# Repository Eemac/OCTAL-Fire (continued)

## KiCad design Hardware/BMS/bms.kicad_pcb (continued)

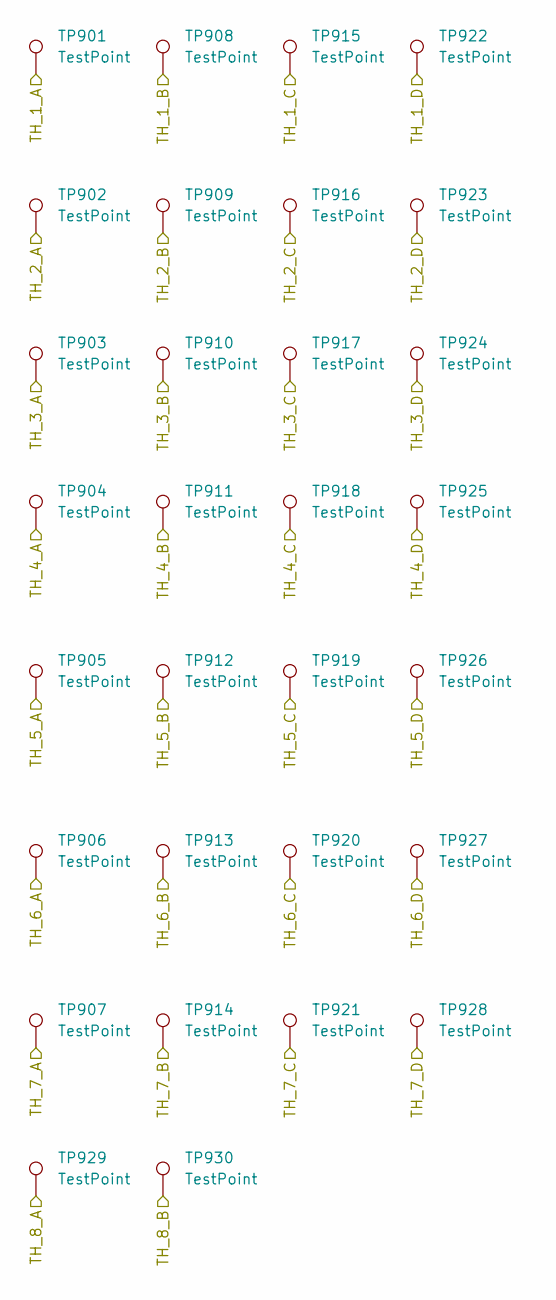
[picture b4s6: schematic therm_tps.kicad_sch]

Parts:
TP901, TP902, TP903, TP904, TP905, TP906, TP907, TP908, TP909, TP910, TP911, TP912, TP913, TP914, TP915, TP916, TP917, TP918, TP919, TP920, TP921, TP922, TP923, TP924, TP925, TP926, TP927, TP928, TP929, TP930: TestPoint; TestPoint_Pad_1.0x1.0mm

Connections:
/THERM_BUSBAR: TP929.1; also elsewhere on the board
/Thermistors/THERM_AMBIENT: TP930.1; also elsewhere on the board
/Thermistors/TH_1_A: TP901.1; also elsewhere on the board
/Thermistors/TH_1_B: TP908.1; also elsewhere on the board
/Thermistors/TH_1_C: TP915.1; also elsewhere on the board
/Thermistors/TH_1_D: TP922.1; also elsewhere on the board
/Thermistors/TH_2_A: TP902.1; also elsewhere on the board
/Thermistors/TH_2_B: TP909.1; also elsewhere on the board
/Thermistors/TH_2_C: TP916.1; also elsewhere on the board
/Thermistors/TH_2_D: TP923.1; also elsewhere on the board
/Thermistors/TH_3_A: TP917.1; also elsewhere on the board
/Thermistors/TH_3_B: TP924.1; also elsewhere on the board
/Thermistors/TH_3_C: TP903.1; also elsewhere on the board
/Thermistors/TH_3_D: TP910.1; also elsewhere on the board
/Thermistors/TH_4_A: TP904.1; also elsewhere on the board
/Thermistors/TH_4_B: TP911.1; also elsewhere on the board
/Thermistors/TH_4_C: TP918.1; also elsewhere on the board
/Thermistors/TH_4_D: TP925.1; also elsewhere on the board
/Thermistors/TH_5_A: TP905.1; also elsewhere on the board
/Thermistors/TH_5_B: TP912.1; also elsewhere on the board
/Thermistors/TH_5_C: TP919.1; also elsewhere on the board
/Thermistors/TH_5_D: TP926.1; also elsewhere on the board
/Thermistors/TH_6_A: TP906.1; also elsewhere on the board
/Thermistors/TH_6_B: TP913.1; also elsewhere on the board
/Thermistors/TH_6_C: TP920.1; also elsewhere on the board
/Thermistors/TH_6_D: TP927.1; also elsewhere on the board

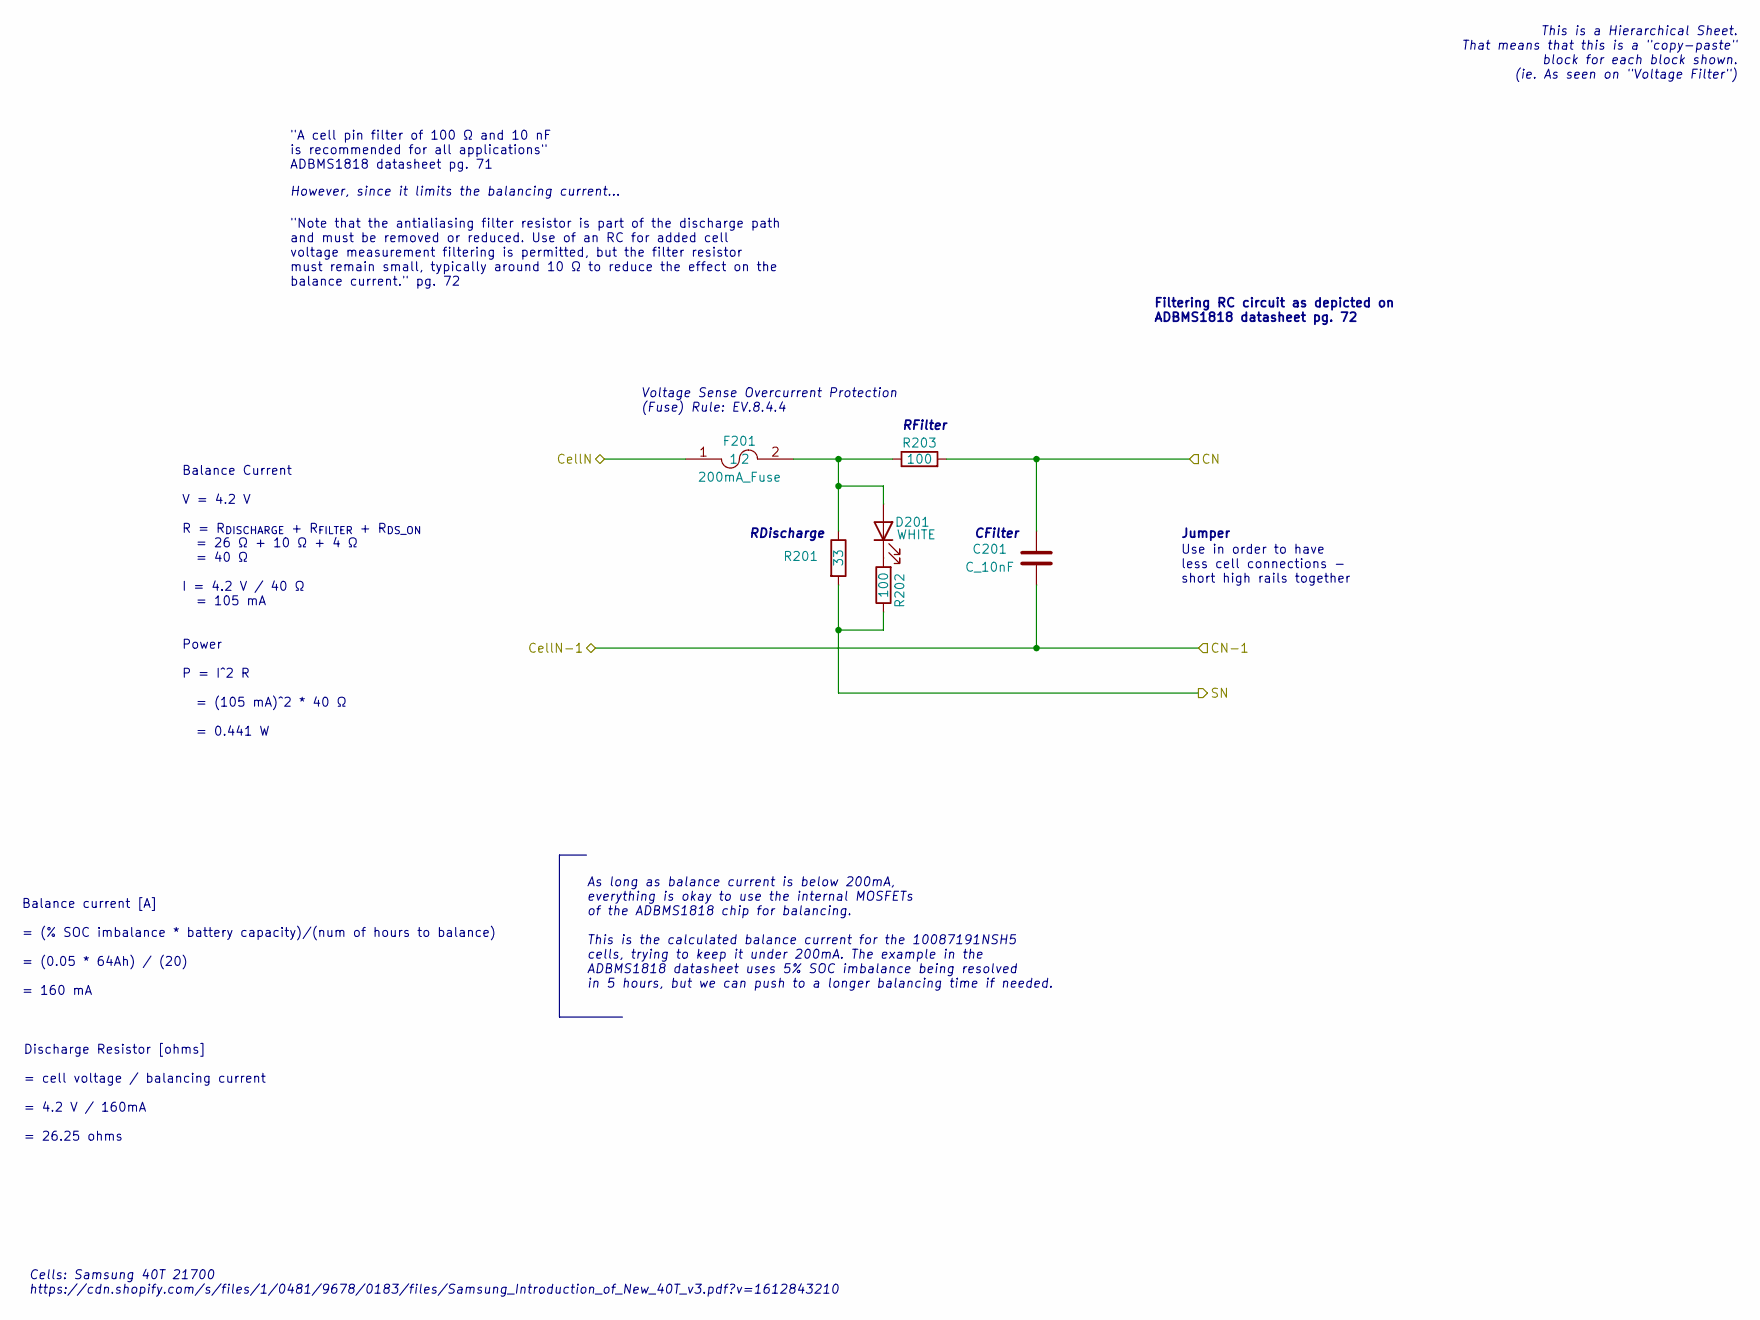
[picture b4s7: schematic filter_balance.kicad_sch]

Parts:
C201: C_10nF; C_0603_1608Metric; MPN CL10B103KB8NNNC
D201: WHITE; LED_0805_2012Metric
F201: 200mA_Fuse; Fuse_1206_3216Metric; MPN 0466.200NRHF
R201: 33; R_2512_6332Metric; MPN 352022RJT
R202: 100; R_0603_1608Metric
R203: 100; R_0603_1608Metric; MPN SG73P1JTTD100J

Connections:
/ADBMS1818/C1: C201.1, F201.1, R203.2; also elsewhere on the board
/ADBMS1818/S1: R201.2, R202.1; also elsewhere on the board
GND: C201.2; also elsewhere on the board
unnamed: D201.2 (A), F201.2, R201.1, R203.1
unnamed: D201.1 (K), R202.2

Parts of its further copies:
C701, C1001, C1201, C1301, C1401, C1501, C1601, C1701, C1801, C1901, C2001, C2101, C2201: C_10nF; C_0603_1608Metric; MPN CL10B103KB8NNNC
D701, D1001, D1201, D1301, D1401, D1501, D1601, D1701, D1801, D1901, D2001, D2101, D2201: WHITE; LED_0805_2012Metric
F701, F1001, F1201, F1301, F1401, F1501, F1601, F1701, F1801, F1901, F2001, F2101, F2201: 200mA_Fuse; Fuse_1206_3216Metric; MPN 0466.200NRHF
R701, R1001, R1201, R1301, R1401, R1501, R1601, R1701, R1801, R1901, R2001, R2101, R2201: 33; R_2512_6332Metric; MPN 352022RJT
R702, R1002, R1202, R1302, R1402, R1502, R1602, R1702, R1802, R1902, R2002, R2102, R2202: 100; R_0603_1608Metric
R703, R1003, R1203, R1303, R1403, R1503, R1603, R1703, R1803, R1903, R2003, R2103, R2203: 100; R_0603_1608Metric; MPN SG73P1JTTD100J

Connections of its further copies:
/ADBMS1818/C1: C701.2; also elsewhere on the board
/ADBMS1818/C2: C701.1, C1001.2, F701.1, R703.2; also elsewhere on the board
/ADBMS1818/C3: C1001.1, C1201.2, F1001.1, R1003.2; also elsewhere on the board
/ADBMS1818/C4: C1201.1, C1301.2, F1201.1, R1203.2; also elsewhere on the board
/ADBMS1818/C5: C1301.1, C1401.2, F1301.1, R1303.2; also elsewhere on the board
/ADBMS1818/C6: C1401.1, C1501.2, F1401.1, R1403.2; also elsewhere on the board
/ADBMS1818/C7: C1501.1, C1601.2, F1501.1, R1503.2; also elsewhere on the board
/ADBMS1818/C8: C1601.1, C1701.2, F1601.1, R1603.2; also elsewhere on the board
/ADBMS1818/C9: C1701.1, C1801.2, F1701.1, R1703.2; also elsewhere on the board
/ADBMS1818/C10: C1801.1, C1901.2, F1801.1, R1803.2; also elsewhere on the board
/ADBMS1818/C11: C1901.1, C2001.2, F1901.1, R1903.2; also elsewhere on the board
/ADBMS1818/C12: C2001.1, C2101.2, F2001.1, R2003.2; also elsewhere on the board
/ADBMS1818/C13: C2101.1, C2201.2, F2101.1, R2103.2; also elsewhere on the board
/ADBMS1818/C14: C2201.1, R2203.2; also elsewhere on the board
/ADBMS1818/CELL14: F2201.1; also elsewhere on the board
/ADBMS1818/S2: R701.2, R702.1; also elsewhere on the board
/ADBMS1818/S3: R1001.2, R1002.1; also elsewhere on the board
/ADBMS1818/S4: R1201.2, R1202.1; also elsewhere on the board
/ADBMS1818/S5: R1301.2, R1302.1; also elsewhere on the board
/ADBMS1818/S6: R1401.2, R1402.1; also elsewhere on the board
/ADBMS1818/S7: R1501.2, R1502.1; also elsewhere on the board
/ADBMS1818/S8: R1601.2, R1602.1; also elsewhere on the board
/ADBMS1818/S9: R1701.2, R1702.1; also elsewhere on the board
/ADBMS1818/S10: R1801.2, R1802.1; also elsewhere on the board
/ADBMS1818/S11: R1901.2, R1902.1; also elsewhere on the board
/ADBMS1818/S12: R2001.2, R2002.1; also elsewhere on the board
/ADBMS1818/S13: R2101.2, R2102.1; also elsewhere on the board
/ADBMS1818/S14: R2201.2, R2202.1; also elsewhere on the board
unnamed: D701.2 (A), F701.2, R701.1, R703.1
unnamed: D701.1 (K), R702.2
unnamed: D1001.2 (A), F1001.2, R1001.1, R1003.1
unnamed: D1001.1 (K), R1002.2
unnamed: D1201.2 (A), F1201.2, R1201.1, R1203.1
unnamed: D1201.1 (K), R1202.2
unnamed: D1301.2 (A), F1301.2, R1301.1, R1303.1
unnamed: D1301.1 (K), R1302.2
unnamed: D1401.2 (A), F1401.2, R1401.1, R1403.1
unnamed: D1401.1 (K), R1402.2
unnamed: D1501.2 (A), F1501.2, R1501.1, R1503.1
unnamed: D1501.1 (K), R1502.2
unnamed: D1601.2 (A), F1601.2, R1601.1, R1603.1
unnamed: D1601.1 (K), R1602.2
unnamed: D1701.2 (A), F1701.2, R1701.1, R1703.1
unnamed: D1701.1 (K), R1702.2
unnamed: D1801.2 (A), F1801.2, R1801.1, R1803.1
unnamed: D1801.1 (K), R1802.2
unnamed: D1901.2 (A), F1901.2, R1901.1, R1903.1
unnamed: D1901.1 (K), R1902.2
unnamed: D2001.2 (A), F2001.2, R2001.1, R2003.1
unnamed: D2001.1 (K), R2002.2
unnamed: D2101.2 (A), F2101.2, R2101.1, R2103.1
unnamed: D2101.1 (K), R2102.2
unnamed: D2201.2 (A), F2201.2, R2201.1, R2203.1
unnamed: D2201.1 (K), R2202.2

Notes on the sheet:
Filtering RC circuit as depicted on ADBMS1818 datasheet pg. 72
"A cell pin filter of 100 Ω and 10 nF is recommended for all applications" ADBMS1818 datasheet pg. 71
Cells: Samsung 40T 21700 https://cdn.shopify.com/s/files/1/0481/9678/0183/files/Samsung_Introduction_of_New_40T_v3.pdf?v=1612843210
Balance current [A] = (% SOC imbalance * battery capacity)/(num of hours to balance) = (0.05 * 64Ah) / (20) = 160 mA
RFilter
Discharge Resistor [ohms] = cell voltage / balancing current = 4.2 V / 160mA = 26.25 ohms
Use in order to have less cell connections - short high rails together
"Note that the antialiasing filter resistor is part of the discharge path and must be removed or reduced. Use of an RC for added cell voltage measurement filtering is permitted, but the filter resistor must remain small, typically around 10 Ω to reduce the effect on the balance current." pg. 72
However, since it limits the balancing current...
RDischarge
Balance Current V = 4.2 V R = R_{DISCHARGE} + R_{FILTER} + R_{DS_ON} = 26 Ω + 10 Ω + 4 Ω = 40 Ω I = 4.2 V / 40 Ω = 105 mA Power P = I^2 R = (105 mA)^2 * 40 Ω = 0.441 W
As long as balance current is below 200mA, everything is okay to use the internal MOSFETs of the ADBMS1818 chip for balancing. This is the calculated balance current for the 10087191NSH5 cells, trying to keep it under 200mA. The example in the ADBMS1818 datasheet uses 5% SOC imbalance being resolve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
This is a Hierarchical Sheet. That means that this is a "copy-paste" block for each block shown. (ie. As seen on "Voltage Filter")
CFilter
Voltage Sense Overcurrent Protection (Fuse) Rule: EV.8.4.4
Jumper

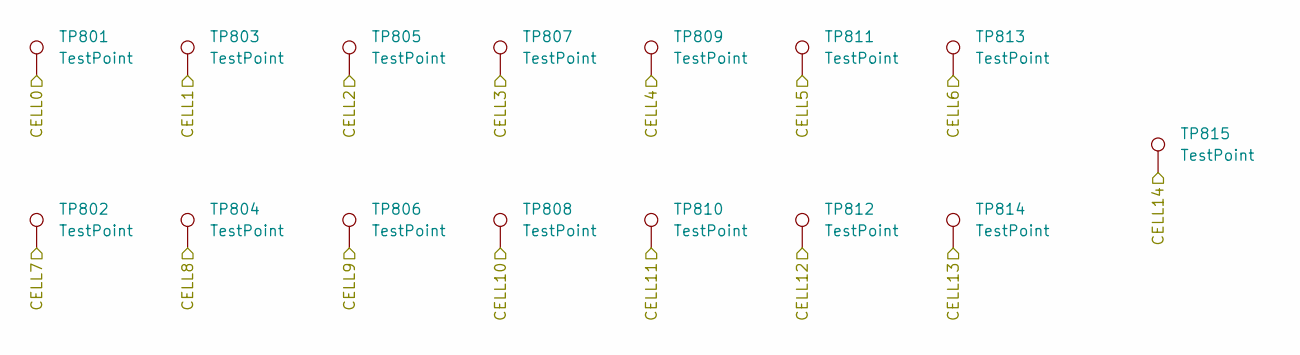
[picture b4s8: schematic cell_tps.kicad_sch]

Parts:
TP801, TP802, TP803, TP804, TP805, TP806, TP807, TP808, TP809, TP810, TP811, TP812, TP813, TP814, TP815: TestPoint; TestPoint_Keystone_5019_Miniature

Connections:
/ADBMS1818/C1: TP803.1; also elsewhere on the board
/ADBMS1818/C2: TP805.1; also elsewhere on the board
/ADBMS1818/C3: TP807.1; also elsewhere on the board
/ADBMS1818/C4: TP809.1; also elsewhere on the board
/ADBMS1818/C5: TP811.1; also elsewhere on the board
/ADBMS1818/C6: TP813.1; also elsewhere on the board
/ADBMS1818/C7: TP802.1; also elsewhere on the board
/ADBMS1818/C8: TP804.1; also elsewhere on the board
/ADBMS1818/C9: TP806.1; also elsewhere on the board
/ADBMS1818/C10: TP808.1; also elsewhere on the board
/ADBMS1818/C11: TP810.1; also elsewhere on the board
/ADBMS1818/C12: TP812.1; also elsewhere on the board
/ADBMS1818/C13: TP814.1; also elsewhere on the board
/ADBMS1818/CELL14: TP815.1; also elsewhere on the board
GND: TP801.1; also elsewhere on the board

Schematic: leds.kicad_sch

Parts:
D1101, D1104, D1106, D1109, D1111: LED_0805_Red; LED_0805_OEM; MPN 475-1415-1-ND
D1102, D1105, D1108, D1110, D1112: LED_0805; LED_0805_OEM; MPN 475-1410-1-ND
D1103: LED_0805_Amber; LED_0805_OEM; MPN L71517CT-ND
D1107: WHITE; LED_0805_2012Metric
R1101, R1104, R1106, R1109, R1111: 300; R_0603_1608Metric; MPN 667-ERJ-6ENF1200V
R1102, R1105, R1108, R1110, R1112: 120; R_0603_1608Metric; MPN 667-ERJ-6ENF1200V
R1103, R1107: 220; R_0603_1608Metric; MPN 667-ERJ-6ENF1200V

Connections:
/STM32/ADBMS_COMS: D1110.2 (A); also elsewhere on the board
/STM32/BMS_HEARTBEAT: D1107.2 (A); also elsewhere on the board
/STM32/CAN_COMS: D1102.2 (A); also elsewhere on the board
/STM32/DEBUG1: D1103.2 (A); also elsewhere on the board
/STM32/ERROR: D1111.2 (A); also elsewhere on the board
/STM32/MUX1_COMS: D1105.2 (A); also elsewhere on the board
/STM32/MUX2_COMS: D1108.2 (A); also elsewhere on the board
/STM32/OT: D1106.2 (A); also elsewhere on the board
/STM32/OV: D1101.2 (A); also elsewhere on the board
/STM32/USB_C_COMS: D1112.2 (A); also elsewhere on the board
/STM32/UT: D1109.2 (A); also elsewhere on the board
/STM32/UV: D1104.2 (A); also elsewhere on the board
GND: R1101.2, R1102.2, R1103.2, R1104.2, R1105.2, R1106.2, R1107.2, R1108.2, R1109.2, R1110.2, R1111.2, R1112.2; also elsewhere on the board
unnamed: D1101.1 (K), R1101.1
unnamed: D1102.1 (K), R1102.1
unnamed: D1103.1 (K), R1103.1
unnamed: D1104.1 (K), R1104.1
unnamed: D1105.1 (K), R1105.1
unnamed: D1106.1 (K), R1106.1
unnamed: D1107.1 (K), R1107.1
unnamed: D1108.1 (K), R1108.1
unnamed: D1109.1 (K), R1109.1
unnamed: D1110.1 (K), R1110.1
unnamed: D1111.1 (K), R1111.1
unnamed: D1112.1 (K), R1112.1

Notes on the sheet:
Heartbeat in code

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
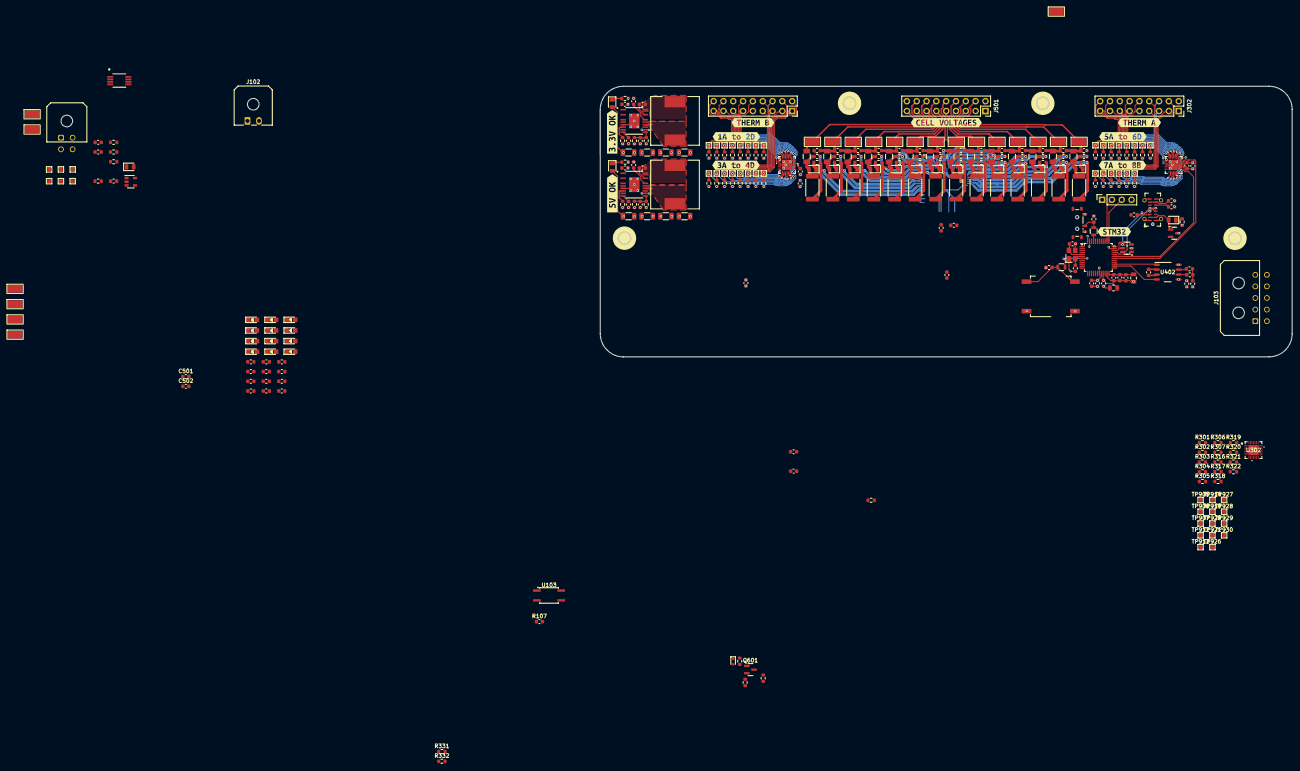
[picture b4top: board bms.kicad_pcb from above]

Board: 6 copper layers, 179.0 x 70.0 mm, 340 parts (1 on the bottom side), 181 nets.

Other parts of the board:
R301#2, R302#2, R303#2, R304#2, R305#2, R306#2, R307#2, R316#2, R317#2, R318#2, R319#2, R320#2, R321#2, R322#2: 100k; R_0603_1608Metric
TP905#2, TP906#2, TP907#2, TP912#2, TP913#2, TP914#2, TP919#2, TP920#2, TP921#2, TP926#2, TP927#2, TP928#2, TP929#2, TP930#2: TestPoint; TestPoint_Pad_1.0x1.0mm
U302#2: MAX14661ETI+T; 21-0139I_T2844-1_MXM
kibuzzard-68FE96E6: G***; kibuzzard-68FE96E6
kibuzzard-68FE9694: G***; kibuzzard-68FE9694
kibuzzard-68FE9708: G***; kibuzzard-68FE9708
kibuzzard-690BEEAD: G***; kibuzzard-690BEEAD
kibuzzard-690BEF4B: G***; kibuzzard-690BEF4B
kibuzzard-690CD8B4: G***; kibuzzard-690CD8B4
kibuzzard-690CF62F: G***; kibuzzard-690CF62F
kibuzzard-690CF63A: G***; kibuzzard-690CF63A
kibuzzard-690CF627: G***; kibuzzard-690CF627
kibuzzard-690D526F: G***; kibuzzard-690D526F

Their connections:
+3.3V: R301#2.2, R302#2.2, R303#2.2, R304#2.2, R305#2.2, R306#2.2, R307#2.2, R316#2.2, R317#2.2, R318#2.2, R319#2.2, R320#2.2, R321#2.2, R322#2.2, U302#2.22 (*SD), U302#2.26 (VCC), U302#2.28 (DOUT/A1); also elsewhere on the board
/MUX_SCL: U302#2.24 (SCLK/SCL); also elsewhere on the board
/MUX_SDA: U302#2.27 (DIN/SDA); also elsewhere on the board
/THERM_A2: U302#2.10 (COMA); also elsewhere on the board
/THERM_B2: U302#2.13 (COMB); also elsewhere on the board
/THERM_BUSBAR: R307#2.1, U302#2.17 (AB13); also elsewhere on the board
/Thermistors/THERM_AMBIENT: R322#2.1, U302#2.16 (AB14); also elsewhere on the board
/Thermistors/TH_5_A: R301#2.1, TP905#2.1, U302#2.2 (AB01); also elsewhere on the board
/Thermistors/TH_5_B: R316#2.1, TP912#2.1, U302#2.3 (AB02); also elsewhere on the board
/Thermistors/TH_5_C: R302#2.1, TP919#2.1, U302#2.4 (AB03); also elsewhere on the board
/Thermistors/TH_5_D: R317#2.1, TP926#2.1, U302#2.5 (AB04); also elsewhere on the board
/Thermistors/TH_6_A: R303#2.1, TP906#2.1, U302#2.6 (AB05); also elsewhere on the board
/Thermistors/TH_6_B: R318#2.1, TP913#2.1, U302#2.7 (AB06); also elsewhere on the board
/Thermistors/TH_6_C: R304#2.1, TP920#2.1, U302#2.8 (AB07); also elsewhere on the board
/Thermistors/TH_6_D: R319#2.1, TP927#2.1, U302#2.9 (AB08); also elsewhere on the board
GND: U302#2.1 (*SPI/I2C), U302#2.11 (GND), U302#2.23 (*CS/A0), U302#2.25 (GND), U302#2.29 (EPAD); also elsewhere on the board

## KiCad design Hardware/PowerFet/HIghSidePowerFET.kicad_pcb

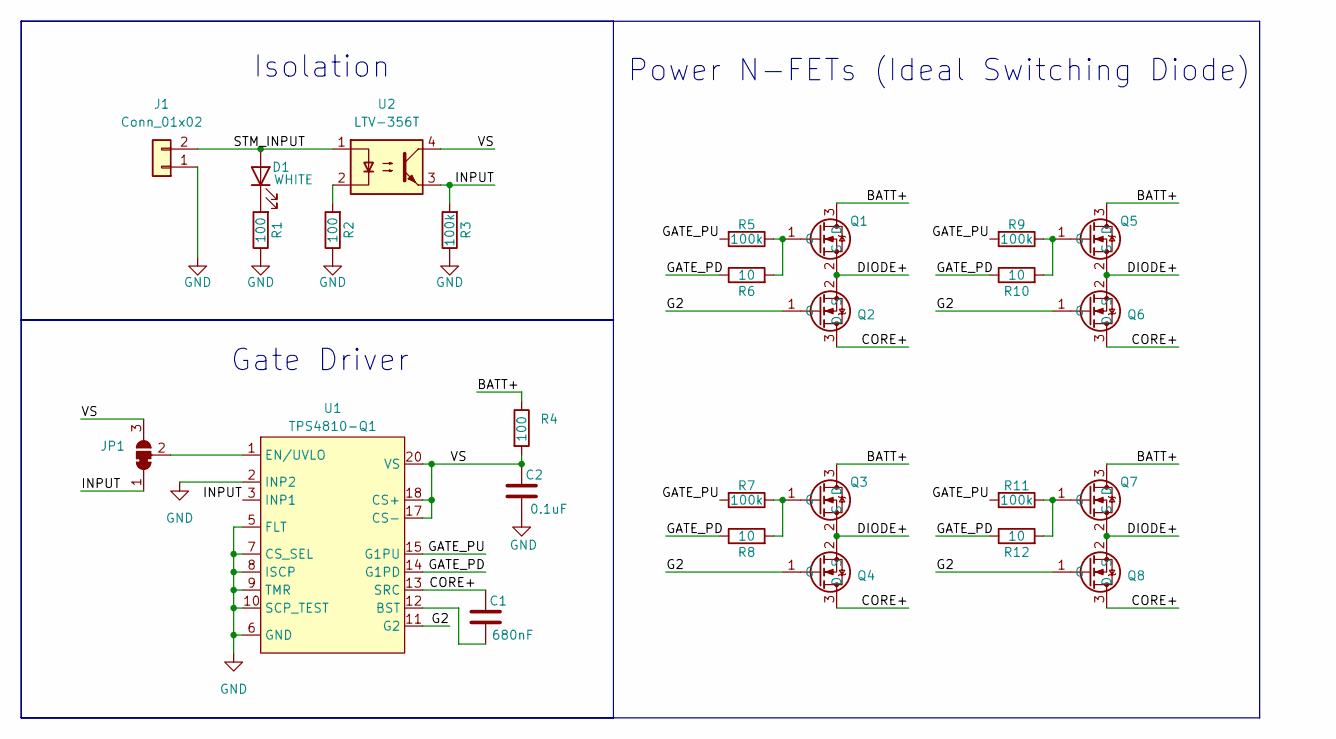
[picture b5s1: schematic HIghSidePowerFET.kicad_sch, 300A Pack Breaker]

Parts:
C1: 680nF; C_0603_1608Metric
C2: 0.1uF; C_0603_1608Metric
D1: WHITE; LED_0805_2012Metric
J1: Conn_01x02; Molex_Nano-Fit_105313-xx02_1x02_P2.50mm_Horizontal
JP1: SolderJumper_3_Bridged12; SolderJumper-3_P1.3mm_Bridged12_RoundedPad1.0x1.5mm
Q1, Q2, Q3, Q4, Q5, Q6, Q7, Q8: NTBLS0D8N08X
R1, R2: 100; R_0603_1608Metric
R3, R5, R7, R9, R11: 100k; R_0603_1608Metric
R4: 100; R_0805_2012Metric
R6, R8, R10, R12: 10; R_0603_1608Metric
U1: TPS4810-Q1; VSSOP-19
U2: LTV-356T; SO-4_4.4x3.6mm_P2.54mm

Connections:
/BATT+: Q1.3 (D), Q3.3 (D), Q5.3 (D), Q7.3 (D), R4.1
/CORE+: C1.2, Q2.3 (D), Q4.3 (D), Q6.3 (D), Q8.3 (D), U1.13 (SRC)
/DIODE+: Q1.2 (S), Q2.2 (S), Q3.2 (S), Q4.2 (S), Q5.2 (S), Q6.2 (S), Q7.2 (S), Q8.2 (S)
/G2: Q2.1 (G), Q4.1 (G), Q6.1 (G), Q8.1 (G), U1.11 (G2)
/GATE_PD: R6.1, R8.1, R10.1, R12.1, U1.14 (G1PD)
/GATE_PU: R5.2, R7.2, R9.2, R11.2, U1.15 (G1PU)
/INPUT: JP1.1 (A), R3.2, U1.3 (INP1), U2.3
/STM_INPUT: D1.2 (A), J1.2, U2.1
/VS: C2.2, JP1.3 (B), R4.2, U1.17 (CS-), U1.18 (CS+), U1.20 (VS), U2.4
GND: C2.1, J1.1, R1.1, R2.1, R3.1, U1.2 (INP2), U1.5 (FLT), U1.6 (GND), U1.7 (CS_SEL), U1.8 (ISCP), U1.9 (TMR), U1.10 (SCP_TEST)
unnamed: D1.1 (K), R1.2
unnamed: JP1.2 (C), U1.1 (EN/UVLO)
unnamed: Q1.1 (G), R5.1, R6.2
unnamed: Q3.1 (G), R7.1, R8.2
unnamed: Q5.1 (G), R9.1, R10.2
unnamed: Q7.1 (G), R11.1, R12.2
unnamed: R2.2, U2.2
unnamed: C1.1, U1.12 (BST)

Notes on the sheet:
Power N-FETs (Ideal Switching Diode)
Gate Driver
Isolation

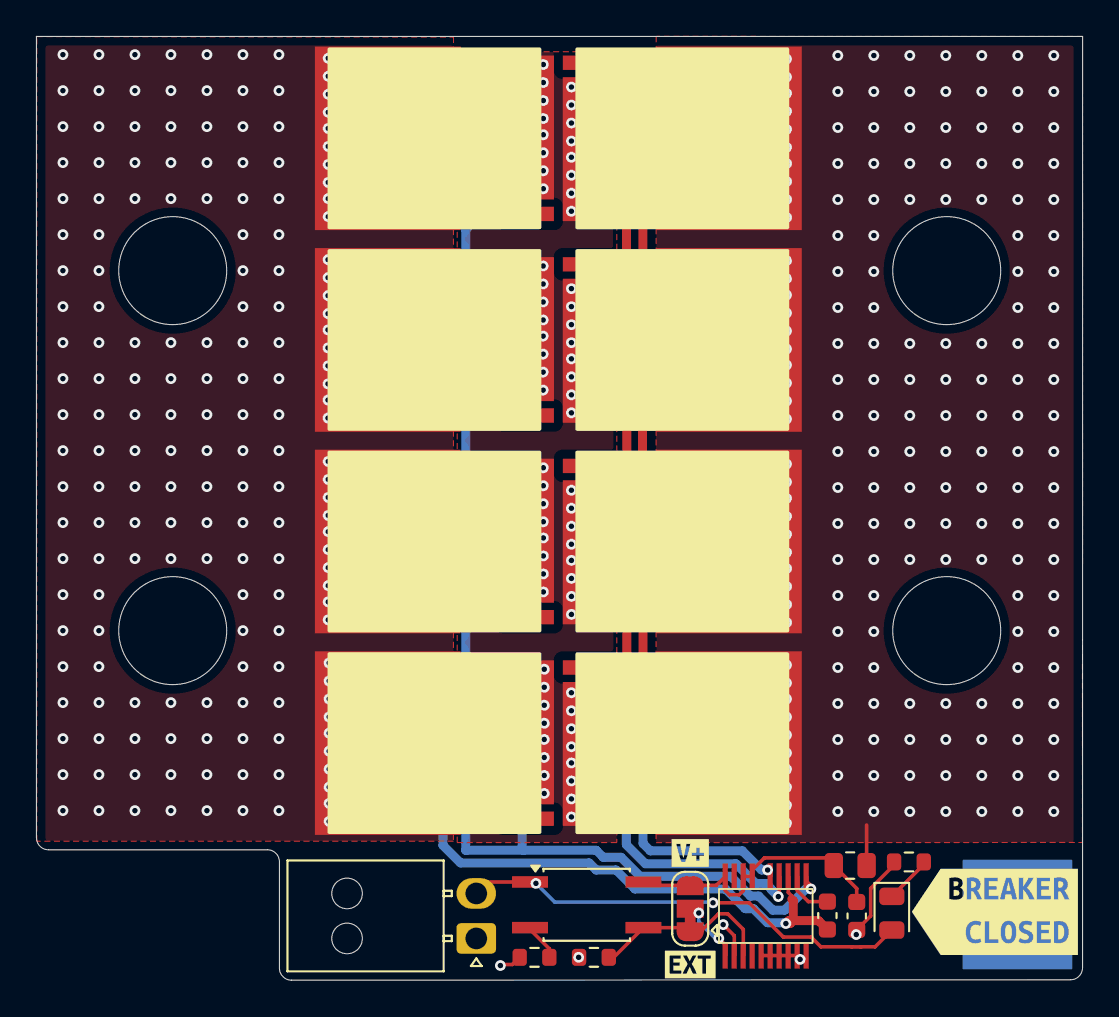
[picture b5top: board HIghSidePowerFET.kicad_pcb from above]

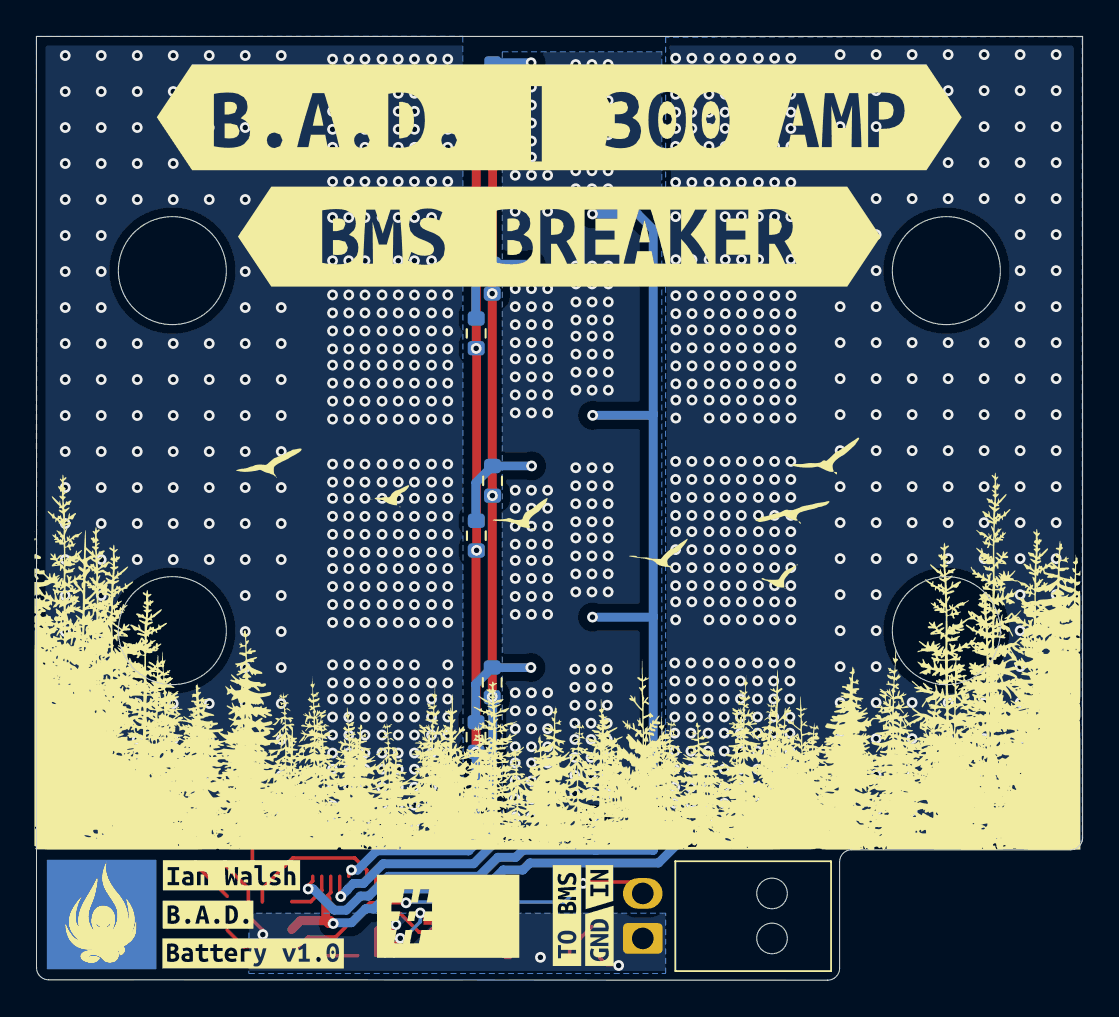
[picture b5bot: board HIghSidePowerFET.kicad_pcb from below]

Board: 2 copper layers, 58.1 x 52.4 mm, 39 parts (17 on the bottom side), 18 nets.

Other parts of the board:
kibuzzard-68F7A0AD: G***; kibuzzard-68F7A0AD
kibuzzard-68F7A0C5: G***; kibuzzard-68F7A0C5
kibuzzard-68F7A12F: G***; kibuzzard-68F7A12F
kibuzzard-68F7D5F0: G***; kibuzzard-68F7D5F0
kibuzzard-68F79DC8: G***; kibuzzard-68F79DC8
kibuzzard-6906AA9C: G***; kibuzzard-6906AA9C
kibuzzard-6906AD14: G***; kibuzzard-6906AD14
kibuzzard-6906C7DA: G***; kibuzzard-6906C7DA
kibuzzard-6906CB2D: G***; kibuzzard-6906CB2D
kibuzzard-6907FFCC: G***; kibuzzard-6907FFCC
kibuzzard-6907FFEA: G***; kibuzzard-6907FFEA
kibuzzard-690797E2: G***; kibuzzard-690797E2

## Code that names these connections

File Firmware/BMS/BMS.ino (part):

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#include <Wire.h>
#include <math.h>

#define LED PB9
#define ERROR_LED PB4
#define TOTAL_IC 1

#define THERM_A1_PIN PA0
#define THERM_B1_PIN PA1
#define THERM_A2_PIN PA2
#define THERM_B2_PIN PA3

#define MUX_SDA_PIN PA8
#define MUX_SCL_PIN PA9

#define MUX1_ADDR 0x4C
#define MUX2_ADDR 0x4E
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#define MAX14661_CMD_A 0x14
#define MAX14661_CMD_B 0x15

#define ISENSE_PIN PB0

cell_asic bms_ic;
FDCAN_HandleTypeDef hfdcan2;
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
void init_thermistors()
{
  pinMode(THERM_A1_PIN, INPUT_ANALOG);
  pinMode(THERM_B1_PIN, INPUT_ANALOG);
  pinMode(THERM_A2_PIN, INPUT_ANALOG);
  pinMode(THERM_B2_PIN, INPUT_ANALOG);

  Wire.setSDA(MUX_SDA_PIN);
  Wire.setSCL(MUX_SCL_PIN);
  Wire.begin();
  Wire.setClock(100000);

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      cell_mv_to_can_10mv(CELL_VOLTAGE_LOW * 1000.0f)
    );

  digitalToggle(PB11);

  return true;
}
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    last_max_current_temp_c = -20.0f;
  }

  float t1 = therm_voltage_to_temp_c(raw_to_therm_voltage(analogRead(THERM_A1_PIN)));
  float t2 = therm_voltage_to_temp_c(raw_to_therm_voltage(analogRead(THERM_B1_PIN)));
  float t3 = therm_voltage_to_temp_c(raw_to_therm_voltage(analogRead(THERM_A2_PIN)));
  float t4 = therm_voltage_to_temp_c(raw_to_therm_voltage(analogRead(THERM_B2_PIN)));

  float temps[4] = {t1, t2, t3, t4};

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
  if (mux1_ok)
  {
    digitalToggle(PB7);
  }

  bool mux2_ok = set_mux_channels(MUX2_ADDR, thermistors_index, thermistors_index + 1);

  if (mux2_ok)
  {
    digitalToggle(PA15);
  }

  if (!mux1_ok || !mux2_ok)
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  OCTAL_Set_Clock();

  pinMode(LED, OUTPUT);
  pinMode(PB1, OUTPUT);
  pinMode(PB2, OUTPUT);
  pinMode(PB3, OUTPUT);
  pinMode(ERROR_LED, OUTPUT);
  pinMode(PB5, OUTPUT);
  pinMode(PB6, OUTPUT);
  pinMode(PB7, OUTPUT);
  pinMode(PB9, OUTPUT);
  pinMode(PB11, OUTPUT);
  pinMode(PB14, OUTPUT);
  pinMode(PB15, OUTPUT);
  pinMode(PA10, OUTPUT);
  pinMode(PA15, OUTPUT);

  digitalWrite(ERROR_LED, LOW);

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  digitalWrite(CS_PIN, HIGH);

  // DISABLE BMS CONTROL OF FETS
  digitalToggle(PA10);

  SPI.begin();
  SPI.beginTransaction(SPISettings(1000000, MSBFIRST, SPI_MODE0));
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  can_send_cell_voltages_1_a(&hfdcan2);
  can_send_cell_voltages_2_a(&hfdcan2);

  digitalToggle(PB2);
}

unsigned long ms50 = 0;
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  if (now - ms200 >= 200)
  {
    ms200 = now;
    digitalToggle(PB9);
  }

  delay(1);
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
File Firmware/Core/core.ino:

#define HAL_FDCAN_MODULE_ENABLED
#define HAL_CORTEX_MODULE_ENABLED


#include "stm32g4xx_hal.h"
#include "stm32g4xx_hal_fdcan.h"
#include "can_api.h"
#include "MCP23S17.h"

// STM32G473CCTx pin defs
#define HEARTBEAT PA8
#define ASENSE_5V PA0
#define ASENSE_3V3 PA1

#define RESET_IO PA10
#define DISP_CS PA9

#define CAN_COMS PB6 
#define USBC_COMS PB7 
#define BOOT0 PB8 

#define CUBE_HANDOFF PB11 
#define RXCAN PB12 
#define TXCAN PB13 

#define CUBE_IO_RESET PB14 
#define CTRL_NONCRIT_CHECK PB15 
#define SENSE_POWER_CYCLE PA15

// MCP Pin Defs
// port B; all unlabeled are input
#define RESET_CUBE_1 8 // out
#define SHDN_REMOTE 9
#define SHDN_TILT 10
#define SHDN_WIRED 11
#define SHDN_FRAME 12
#define SHDN_TSMS 13
#define SHDN_CRIT_RIDER 14
#define SHDN_CTRL_LOBATT 15

// port A; all unlabeled are input
#define DEBUG1 0 // out
#define RESET_CUBE_2 1 // out
#define SHDN_LOWER_RIDER 3
#define SHDN_NUC 2
#define SHDN_BMS_N 4
#define SHDN_BMS_E 5
#define SHDN_BMS_S 6
#define SHDN_BMS_ALL 7

FDCAN_HandleTypeDef hfdcan2;

// CS, MISO, MOSI, SCK
#define CS PA4
#define MISO PA6
#define MOSI PA7
#define SCK PA5

MCP23S17 MCP(CS);

bool mcpbegin = false;

void OCTAL_Set_Clock(void) {
  // set flash latency for target (144MHz -> FLASH_LATENCY_4) and up voltage to HF range
  __HAL_RCC_PWR_CLK_ENABLE();
  HAL_PWREx_ControlVoltageScaling(PWR_REGULATOR_VOLTAGE_SCALE1_BOOST);

  // Request HSE ON (clock source mode from external high-speed crystal)
  RCC->CR |= RCC_CR_HSEON;

  //Move PLL to source off of HSE
  MODIFY_REG(RCC->CFGR, RCC_CFGR_SW, RCC_CFGR_SW_HSE);

  //Setup PLL for 48MHz peripheral clock
  RCC_OscInitTypeDef RCC_OscInitStruct = { 0 };
  RCC_OscInitStruct.OscillatorType = RCC_OSCILLATORTYPE_HSE;
  RCC_OscInitStruct.HSEState = RCC_HSE_ON;
  RCC_OscInitStruct.PLL.PLLState = RCC_PLL_ON;
  RCC_OscInitStruct.PLL.PLLSource = RCC_PLLSOURCE_HSE;
  RCC_OscInitStruct.PLL.PLLM = RCC_PLLM_DIV4;  // 12MHz after div
  RCC_OscInitStruct.PLL.PLLN = 24;             //2ds88Mhz after mult
  RCC_OscInitStruct.PLL.PLLP = RCC_PLLP_DIV2;  //144MHz CPU clock
  RCC_OscInitStruct.PLL.PLLQ = RCC_PLLQ_DIV6;  //Peripherals at 48MHz (required by USB (48MHz only), CAN ahas a bit more leeway)
  RCC_OscInitStruct.PLL.PLLR = RCC_PLLR_DIV2;
  if (HAL_RCC_OscConfig(&RCC_OscInitStruct) != HAL_OK) {
    Error_Handler();
  }

  //Enable PLL
  SET_BIT(RCC->CR, RCC_CR_PLLON);

  //Set CPU and bus clocks to source 144MHz from PLL
  RCC_ClkInitTypeDef RCC_ClkInitStruct = { 0 };
  RCC_ClkInitStruct.ClockType = RCC_CLOCKTYPE_HCLK | RCC_CLOCKTYPE_SYSCLK
                                | RCC_CLOCKTYPE_PCLK1 | RCC_CLOCKTYPE_PCLK2;
  RCC_ClkInitStruct.SYSCLKSource = RCC_SYSCLKSOURCE_PLLCLK;
  RCC_ClkInitStruct.AHBCLKDivider = RCC_SYSCLK_DIV1;
  RCC_ClkInitStruct.APB1CLKDivider = RCC_HCLK_DIV1;
  RCC_ClkInitStruct.APB2CLKDivider = RCC_HCLK_DIV1;

  if (HAL_RCC_ClockConfig(&RCC_ClkInitStruct, FLASH_LATENCY_4) != HAL_OK) {
    Error_Handler();
  }

  //push new clock settings to time-dependent code/structs
  SystemCoreClockUpdate();

  //Start tick counter
  HAL_InitTick(TICK_INT_PRIORITY);
}

void setup() {
  pinMode(HEARTBEAT, OUTPUT);  // Core Heartbeat
  digitalWrite(HEARTBEAT, HIGH);

  // delay(20000);

  pinMode(RESET_IO, OUTPUT);
  digitalWrite(RESET_IO, HIGH); // SO IMPORTANT TO HAVE BEFORE MCPBEGIN

  pinMode(CUBE_HANDOFF, OUTPUT);
  digitalWrite(CUBE_HANDOFF, LOW);

  Serial.begin(112500);
  delay(5000);

  OCTAL_Set_Clock();
  delay(10);

  pinMode(CAN_COMS, OUTPUT);
  pinMode(USBC_COMS, OUTPUT);
  pinMode(BOOT0, INPUT);

  
  pinMode(RXCAN, INPUT);
  pinMode(TXCAN, OUTPUT);

  // pinMode(CUBE_IO_RESET, OUTPUT);
  pinMode(CTRL_NONCRIT_CHECK, OUTPUT);
  pinMode(SENSE_POWER_CYCLE, OUTPUT);


  pinMode(DISP_CS, OUTPUT);
  digitalWrite(DISP_CS, HIGH);

  SPI.begin();
  // mcpbegin = MCP.begin();
  delay(50);

  if (mcpbegin) {
    MCP.pinMode1(DEBUG1, OUTPUT);
    MCP.pinMode1(RESET_CUBE_2, OUTPUT);

    // GPB output: RESET_CUBE_1
    MCP.pinMode1(RESET_CUBE_1, OUTPUT);

    // everything else input (SHDN signals)
    MCP.pinMode1(SHDN_REMOTE, INPUT);
    MCP.pinMode1(SHDN_TILT, INPUT);
    MCP.pinMode1(SHDN_WIRED, INPUT);
    MCP.pinMode1(SHDN_FRAME, INPUT);
    MCP.pinMode1(SHDN_TSMS, INPUT);
    MCP.pinMode1(SHDN_CRIT_RIDER, INPUT);
    MCP.pinMode1(SHDN_CTRL_LOBATT, INPUT);

    MCP.pinMode1(SHDN_LOWER_RIDER, INPUT);
    MCP.pinMode1(SHDN_NUC, INPUT);
    MCP.pinMode1(SHDN_BMS_N, INPUT);
    MCP.pinMode1(SHDN_BMS_E, INPUT);
    MCP.pinMode1(SHDN_BMS_S, INPUT);
    MCP.pinMode1(SHDN_BMS_ALL, INPUT);
    // // Port 0 (GPA): Debug GPA0, ResetCube2 GPA1 are Outputs (0), others are SHDN Inputs (1)
    // MCP.pinMode8(0, 0b11111100);   
    // // Port 1 (GPB): ResetCube1 GPB0 is Output (0), others are SHDN Inputs (1)
    // MCP.pinMode8(1, 0b11111110); 
  
    Serial.println("MCP23S17 Initialized.");
  } else {
    Serial.println("MCP23S17 not found.");
  }

  can_init_core(&hfdcan2);
}

uint16_t parsedValue = 0;
float current_5v = 0;
float current_3v3 = 0;

// const int shdnPins[] = {
//   SHDN_N, SHDN_NE, SHDN_E, SHDN_SE, 
//   SHDN_S, SHDN_SW, SHDN_W, SHDN_NW
// };
// const char* shdnLabels[] = {
//   "N ", "NE", "E ", "SE", 
//   "S ", "SW", "W ", "NW"
// };

void printShutdownStatus() {
    if (mcpbegin) {
    Serial.println("--- MCP SHDN Status ---");

    const int mcpPins[] = {
      SHDN_REMOTE,
      SHDN_TILT,
      SHDN_WIRED,
      SHDN_FRAME,
      SHDN_TSMS,
      SHDN_CRIT_RIDER,
      SHDN_CTRL_LOBATT,

      SHDN_LOWER_RIDER,
      SHDN_NUC,
      SHDN_BMS_N,
      SHDN_BMS_E,
      SHDN_BMS_S,
      SHDN_BMS_ALL
    };

    const char* mcpLabels[] = {
      "REMOTE",
      "TILT",
      "WIRED",
      "FRAME",
      "TSMS",
      "CRIT",
      "LOBATT",

      "LOWER",
      "NUC",
      "BMS_N",
      "BMS_E",
      "BMS_S",
      "BMS_ALL"
    };

    for (int i = 0; i < 13; i++) {
      int state = MCP.read1(mcpPins[i]);

      Serial.print(mcpLabels[i]);
      Serial.print(": ");
      Serial.print(state == HIGH ? "CLOSED" : "OPEN");

      if ((i + 1) % 4 == 0) {
        Serial.println();
      } else {
        Serial.print(" | ");
      }
    }

    Serial.println();
  }
  Serial.println();
}
float MAX_VPACK_DIFF = 0.080; // 80mV pack difference
bool try_to_reset = true;

void loop() {

  digitalToggle(HEARTBEAT);
  MCP.write1(RESET_CUBE_1, 0);

  delay(100);
  MCP.write1(DEBUG1, 1);
  delay(100);
  MCP.write1(DEBUG1, 0);
  delay(100);

  // if (try_to_reset) {
  //   Serial.println("Attempting reset");
  //   MCP.write1(RESET_CUBE_1, 0);
  //   delay(100);
  //   try_to_reset = false;
  // }
  // MCP.write1(RESET_CUBE_1, 1);

  current_5v = (analogRead(ASENSE_5V) * 3.3) / 1023.0;
  current_3v3 = (analogRead(ASENSE_3V3) * 3.3) / 1023.0;
  // Serial.print("Current 5V: ");
  // Serial.println(current_5v);
  // Serial.print("Current 3V3: ");
  // Serial.println(current_3v3);

  printShutdownStatus();

  // delay(100);
  core_status.core_state = 0;
  // // Serial.print("DEBUG1 raw read: ");
  // // Serial.println(MCP.read1(DEBUG1), HEX);

  if (Serial.available()) {
    digitalWrite(USBC_COMS, HIGH);
    String input = Serial.readStringUntil('\n');
    input.trim();

    long value = input.toInt();

    if (value >= 0 && value <= 65535) {
      parsedValue = value;

      Serial.print("Parsed uint16_t value: ");
      Serial.println(parsedValue, HEX);
    } else {
      Serial.println("Value out of uint16_t range.");
    }
  } else {
    digitalWrite(USBC_COMS, LOW);
  }

  if (can_receive(&hfdcan2) > 0) {
    Serial.print("CAN RECEIVED");
    digitalWrite(CAN_COMS, HIGH);
    
    // pack voltage reading
    float min_volt = bms_status_n.pack_voltage;
    if (bms_status_e.pack_voltage < min_volt) min_volt = bms_status_e.pack_voltage;
    if (bms_status_s.pack_voltage < min_volt) min_volt = bms_status_s.pack_voltage;
    if (bms_status_w.pack_voltage < min_volt) min_volt = bms_status_w.pack_voltage;

    core_batt_ctrl.north = (bms_status_n.pack_voltage <= (min_volt + MAX_VPACK_DIFF)) ? 1 : 0;
    core_batt_ctrl.east  = (bms_status_e.pack_voltage <= (min_volt + MAX_VPACK_DIFF)) ? 1 : 0;
    core_batt_ctrl.south = (bms_status_s.pack_voltage <= (min_volt + MAX_VPACK_DIFF)) ? 1 : 0;
    core_batt_ctrl.west  = (bms_status_w.pack_voltage <= (min_volt + MAX_VPACK_DIFF)) ? 1 : 0;

    if (core_batt_ctrl == 1111) {
      MCP.write1(DEBUG1, HIGH);
    }
    
    Serial.print(CAN_COMS);
  } else {
    digitalWrite(CAN_COMS, LOW);
  }

  can_send_core_status(&hfdcan2);
  can_send_core_batt_ctrl(&hfdcan2);
}

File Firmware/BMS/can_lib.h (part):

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#define CAN_LIB_BMS_VOLTAGE_METRICS_A_CELL_VOLTAGE_THRESHOLD_HIGH_NAME "cell_voltage_threshold_high"
#define CAN_LIB_BMS_VOLTAGE_METRICS_A_CELL_VOLTAGE_THRESHOLD_LOW_NAME "cell_voltage_threshold_low"
#define CAN_LIB_BMS_VOLTAGE_METRICS_A_CHARGER_TARGET_VOLTAGE_NAME "charger_target_voltage"
#define CAN_LIB_CELL_VOLTAGES_0_A_CELL_1_NAME "cell_1"
#define CAN_LIB_CELL_VOLTAGES_0_A_CELL_2_NAME "cell_2"
#define CAN_LIB_CELL_VOLTAGES_0_A_CELL_3_NAME "cell_3"
#define CAN_LIB_CELL_VOLTAGES_0_A_CELL_4_NAME "cell_4"
#define CAN_LIB_CELL_VOLTAGES_0_A_CELL_5_NAME "cell_5"
#define CAN_LIB_CELL_VOLTAGES_1_A_CELL_6_NAME "cell_6"
#define CAN_LIB_CELL_VOLTAGES_1_A_CELL_7_NAME "cell_7"
#define CAN_LIB_CELL_VOLTAGES_1_A_CELL_8_NAME "cell_8"
#define CAN_LIB_CELL_VOLTAGES_1_A_CELL_9_NAME "cell_9"
#define CAN_LIB_CELL_VOLTAGES_1_A_CELL_10_NAME "cell_10"
#define CAN_LIB_CELL_VOLTAGES_2_A_CELL_11_NAME "cell_11"
#define CAN_LIB_CELL_VOLTAGES_2_A_CELL_12_NAME "cell_12"
#define CAN_LIB_CELL_VOLTAGES_2_A_CELL_13_NAME "cell_13"
#define CAN_LIB_CELL_VOLTAGES_2_A_CELL_14_NAME "cell_14"
#define CAN_LIB_THERMISTORS_0_A_THERMISTOR_1_NAME "thermistor_1"
#define CAN_LIB_THERMISTORS_0_A_THERMISTOR_2_NAME "thermistor_2"
#define CAN_LIB_THERMISTORS_0_A_THERMISTOR_3_NAME "thermistor_3"
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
